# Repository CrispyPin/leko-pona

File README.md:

# leko pona

## Related repos
- [ZMK config](https://github.com/CrispyPin/zmk-config/) (layout based on colemak-dh)
- [Ergogen config](https://github.com/CrispyPin/ergogen/) used to generate the pcb

## Parts list
- nice!nano x2
- 12 pin socket strips x4
- JST-PH battery connectors x2
- PCM12 power switch x2
- 3.7V 130mAh battery x2
- choc switches x36
- choc keycaps x36
- choc hotswap sockets x36 (optional)
- rubber feet (optional)

## Notes about assembly
- Solder pads for the reversible footprint should be soldered on the underside of the board if you want the back of the nice!nano facing up (like in the picture)
- The battery connector is slightly asymmetrical on the two halves, it should be clear from the outline on the silkscreen which way to put it
- If your batteries are small enough you can tuck them under the controllers
- You can use a permanent marker to get a clean look on the edges of the pcbs

## LEGO tenting set
[Instructions](lego_tenting.md)

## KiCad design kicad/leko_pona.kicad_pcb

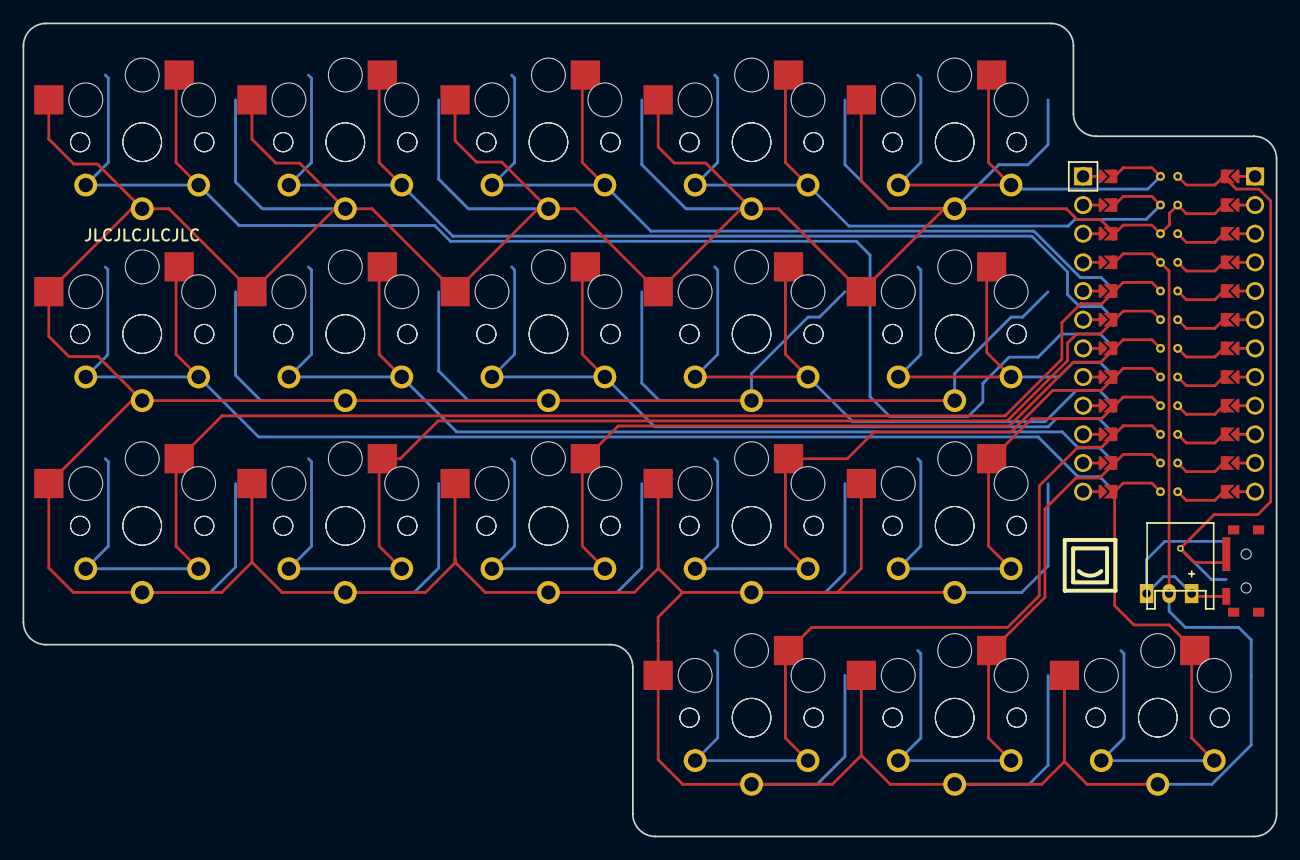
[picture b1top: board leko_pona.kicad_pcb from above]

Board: 2 copper layers, 111.1 x 72.0 mm, 38 parts (0 on the bottom side), 20 nets.

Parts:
JST1: JST_PH_S2B-PH-K_02x2.00mm_Angled
MCU1: ProMicro
S1, S2, S3, S4, S5, S6, S7, S8, S9, S10, S11, S12, S13, S14, S15, S16, S17, S18, S19, S20, S21, S22, S23, S24, S25, S26, S27, S28, S29, S30, S31, S32, S33, S34, S35, S36: PG1350

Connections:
GND: JST1.2, MCU1.2, MCU1.21, MCU1.22, S1.2, S2.2, S3.2, S4.2, S5.2, S6.2, S7.2, S8.2, S9.2, S10.2, S11.2, S12.2, S13.2, S14.2, S15.2, S16.2, S17.2, S18.2, S19.2, S20.2, S21.2, S22.2, S23.2, S24.2, S25.2, S26.2, S27.2, S28.2, S29.2, S30.2, S31.2, S32.2, S33.2, S34.2, S35.2, S36.2
main_index_bottom: MCU1.17, S19.1, S20.1
main_index_home: MCU1.9, S21.1, S22.1
main_index_top: MCU1.23, S23.1, S24.1
main_inner_bottom: MCU1.16, S25.1, S26.1
main_inner_home: MCU1.8, S27.1, S28.1
main_inner_top: MCU1.24, S29.1, S30.1
main_middle_bottom: MCU1.18, S13.1, S14.1
main_middle_home: MCU1.10, S15.1, S16.1
main_middle_top: MCU1.5, S17.1, S18.1
main_pinky_bottom: MCU1.20, S1.1, S2.1
main_pinky_home: MCU1.12, S3.1, S4.1
main_pinky_top: MCU1.7, S5.1, S6.1
main_ring_bottom: MCU1.19, S7.1, S8.1
main_ring_home: MCU1.11, S9.1, S10.1
main_ring_top: MCU1.6, S11.1, S12.1
pos: JST1.1, JST1.3
thumb_middle_default: MCU1.14, S33.1, S34.1
thumb_reachy_default: MCU1.13, S35.1, S36.1
thumb_tucky_default: MCU1.15, S31.1, S32.1

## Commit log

2022-10-01 add pcb files
2022-10-01 add images
2022-10-01 move gerber zip
2022-10-21 Add part list and assembly notes to readme
2022-10-26 add lego tenting set instructions
2022-10-26 move kicad files to folder
2023-08-26 add new image
2024-04-15 add cad files for keyboard and case prototype
